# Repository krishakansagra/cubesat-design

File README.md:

# cubesat-design
transmitting data from cubesat to receive at base station

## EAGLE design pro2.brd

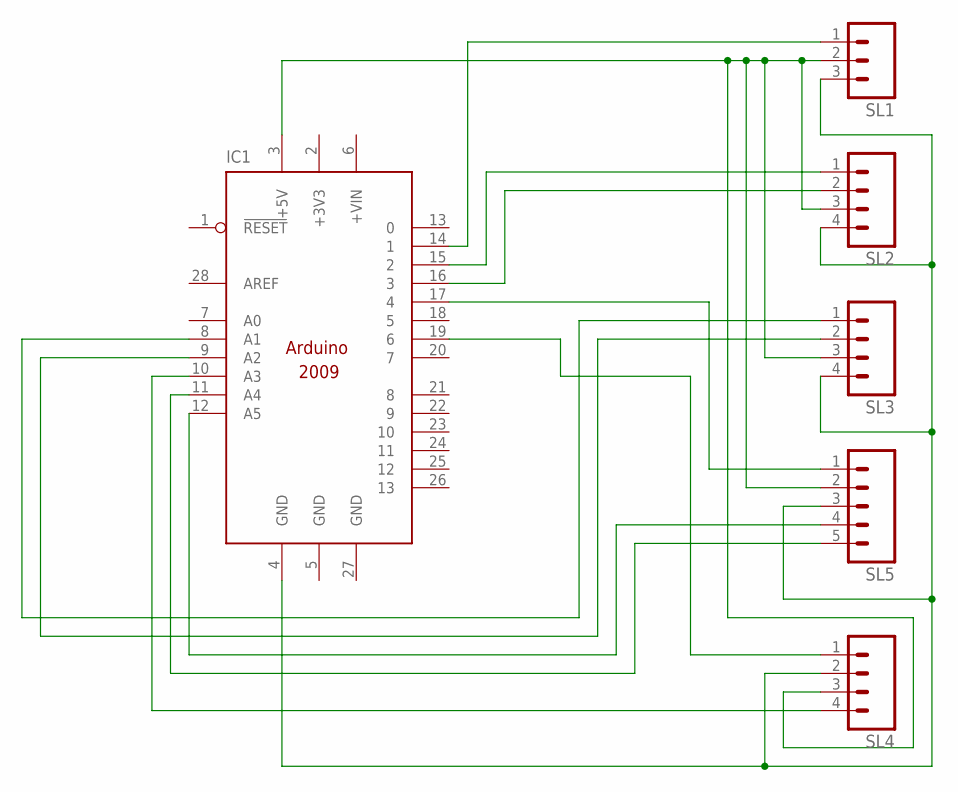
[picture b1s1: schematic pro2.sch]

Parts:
IC1: ARDUINO2009_10; ARDUINO2009
SL1: M03; 03P
SL2, SL3, SL4: M04; 04P
SL5: M05; 05P

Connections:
+3V3: IC1.2 (+3V3)
GND: IC1.5 (GND), IC1.27 (GND)
unnamed: IC1.12 (A5), SL5.4
unnamed: IC1.14 (1), SL1.1
unnamed: IC1.15 (2), SL2.1
unnamed: IC1.16 (3), SL2.2
unnamed: IC1.3 (+5V), SL1.2, SL2.3, SL3.3, SL4.3, SL5.2
unnamed: IC1.4 (GND), SL1.3, SL2.4, SL3.4, SL4.2, SL5.3
unnamed: IC1.8 (A1), SL3.1
unnamed: IC1.9 (A2), SL3.2
unnamed: IC1.11 (A4), SL5.5
unnamed: IC1.17 (4), SL5.1
unnamed: IC1.19 (6), SL4.1
unnamed: IC1.10 (A3), SL4.4

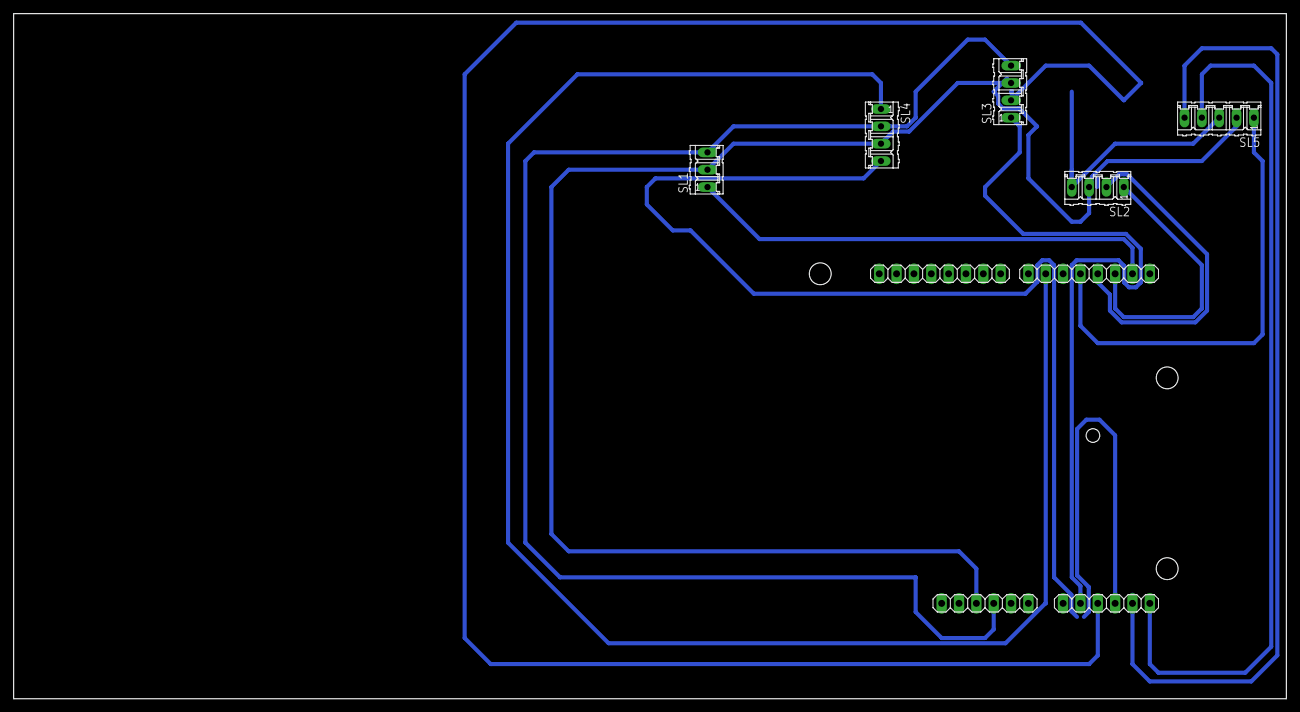
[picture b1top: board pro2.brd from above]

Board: 2 copper layers, 186.4 x 100.3 mm, 6 parts (0 on the bottom side), 13 nets.

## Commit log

2025-12-24 Create transmitter
    code at transmitting side
2025-12-24 Create receiver
